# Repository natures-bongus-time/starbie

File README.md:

# Starbie

Starbie is a tiny motion-controlled digital pet
## What it is

It's a tamagotchi-like pet that has two keys, a screen and a temperature and humidity sensor, and it's based off of a [starboy](https://lilguy.net)

## Features
- It can tell you the temperature with a dht 11 sensor
- sense motions with an accelerometer
- it has stats that you have to keep up to keep it happy, which are programmed on Arduino ide
- be fed, play, sleep and more all of which are animations selectable from a motion controlled radial menu
- it will react if you shake it from the motion sensor, but it doesn't really like that

## Why?

This project was created for my week 1 beginner project for [half-life](https://halflife.hackclub.com/)!
I chose it because I'm super new to hardware, so the project guide was super helpful. I wanted to learn how to make projects like this because it's a new and interesting challenge that is super engaging for me, and I had a lot of fun with it.

## Project status

the design and firmware are included, and they're both finished.
## Software

[`Firmware/`](Firmware/) contains one self-contained Arduino IDE sketch for the XIAO ESP32-C3. I added some code and keyboard compatibility.
## Images

above: renders of the PCB
below: the schematic

above: some of the firmware
below: the PCB design/routing

# BOM

|Item                   |Qty,      |Supplier    |,Cost/item,|Total Cost|link                                                                                      |
|-----------------------|----------|------------|-----------|----------|------------------------------------------------------------------------------------------|
|XIAO ESP32 C3          |1         |Seeedstudio |$5.00      |          |https://www.seeedstudio.com/Seeed-XIAO-ESP32C3-p-5431.html                                |
|0.96 OLED              |1         |digikey     |$5.00      |$5.00     |https://www.digikey.com/en/products/detail/universal-solder-electronics-ltd/26377/16822115|
|3647-26098-ND          |1         |digikey     |$2.75      |$2.75     |https://www.digikey.com/en/products/detail/universal-solder-electronics-ltd/26098/26606388|
|DHT11                  |1         |digikey     |$2.39      |$2.39     |https://www.digikey.com/en/products/detail/universal-solder-electronics-ltd/26085/16822119|
|MX Switches            |2         |digikey     |$0.89      |$1.78     |https://www.digikey.com/en/products/detail/e-switch/TL2201OAYA/583531                     |
|10k Resistor           |1         |digikey     |$0.20      |$0.20     |https://www.digikey.com/en/products/detail/stackpole-electronics-inc/CF14JT10K0/1741265   |
|PCB                    |1         |JLCPCB      |$7.10      |$7.10     |https://www.jlcpcb.com/                                                                   |
Estimated total shipping|          |            |           |$5.00     |                                                                                          |

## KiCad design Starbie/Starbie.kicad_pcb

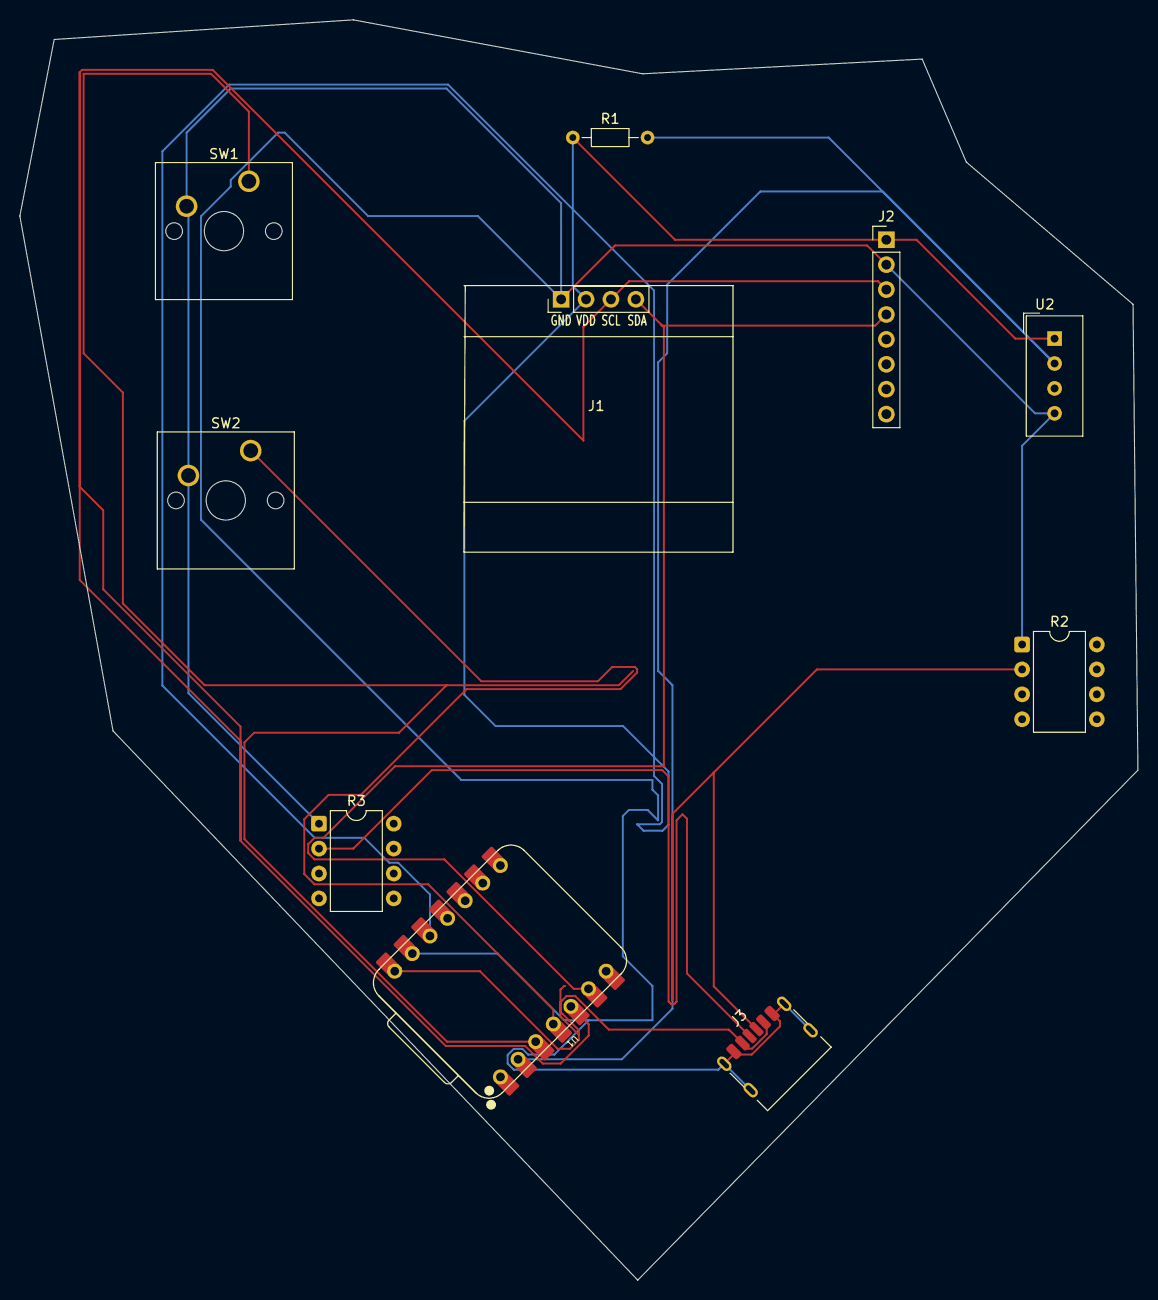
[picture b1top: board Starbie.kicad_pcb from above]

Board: 2 copper layers, 114.0 x 128.5 mm, 10 parts (0 on the bottom side), 10 nets.

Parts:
J1: Conn_01x04_Pin; Display_128x64_096_I2C
J2: Conn_01x08_Pin; PinHeader_1x08_P2.54mm_Vertical
J3: USB_C_Receptacle_USB2.0_14P; USB_C_Receptacle_HRO_TYPE-C-31-M-17
R1: 10K; R_Axial_DIN0204_L3.6mm_D1.6mm_P7.62mm_Horizontal
R2, R3: 5k; DIP-8_W7.62mm
SW1, SW2: SW_Push; SW_Cherry_MX_1.00u_PCB
U1: XIAO-ESP32-C3-SMD; XIAO-ESP32-C6-DIP
U2: DHT11; Aosong_DHT11_5.5x12.0_P2.54mm

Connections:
+3.3V: J1.2, J2.1, R1.1, U1.12 (3V3_OUT), U2.1 (VDD)
+5V: J3.A9 (VBUS), J3.B9 (VBUS), U1.14 (VBUS)
/DHT11 DATA: R1.2, U1.2 (D1), U2.2 (DATA)
/GPI02: SW1.1, U1.3 (D2)
/GPIO3: SW2.1, U1.4 (D3)
/SCL: J1.3, J2.3, U1.5 (D4)
/SDA: J1.4, J2.4, U1.6 (D5)
/groundi: J3.B5 (CC2), R2.2
/ng: J3.A5 (CC1), R3.2
GND: J1.1, J2.2, J3.A12 (GND), J3.B12 (GND), J3.SH (SHIELD), R2.1, R3.1, SW1.2, SW2.2, U1.13 (GND), U2.4 (GND)
